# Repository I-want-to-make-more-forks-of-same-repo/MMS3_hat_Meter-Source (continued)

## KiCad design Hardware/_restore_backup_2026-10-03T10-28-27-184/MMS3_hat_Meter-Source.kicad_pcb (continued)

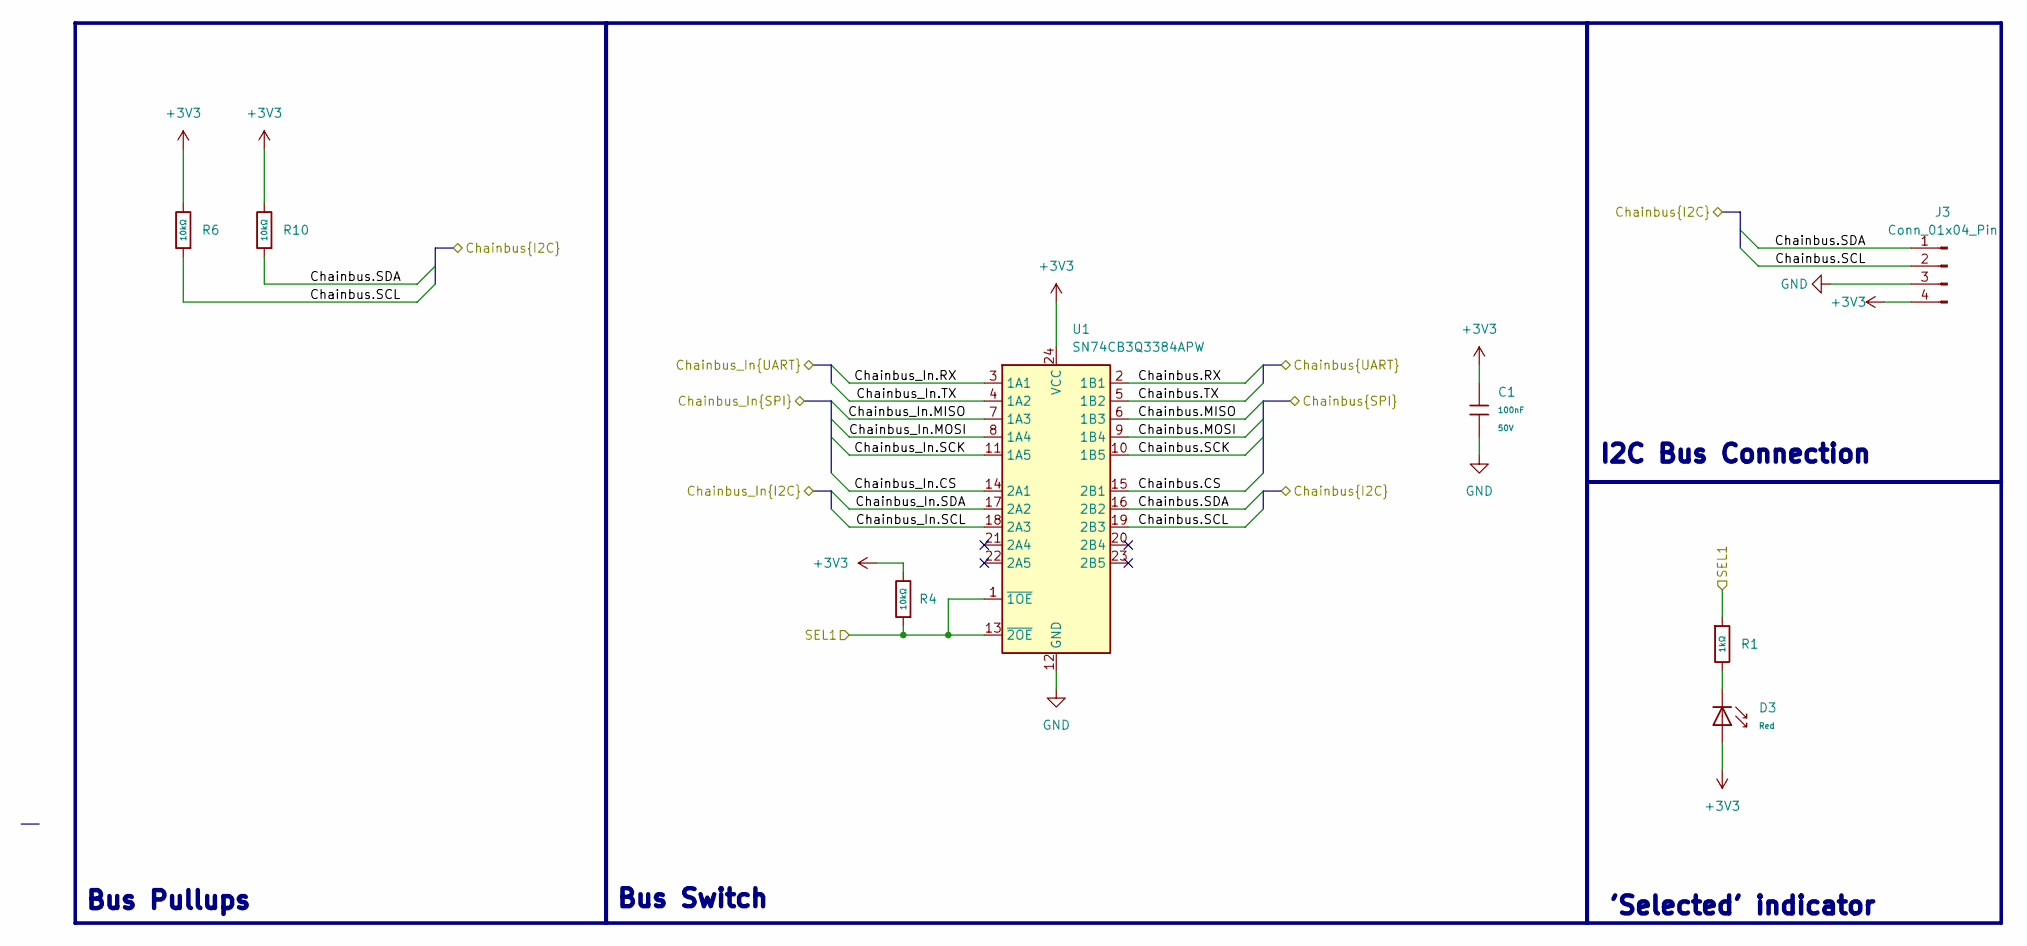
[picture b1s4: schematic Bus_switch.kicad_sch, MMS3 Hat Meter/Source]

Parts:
C1: 100nF; C_0603; Voltage Rated 50V; Tolerance ±10%; Part CC0603KRX7R9BB104; LCSC C14663
D3: Red; D_0603; Part KT-0603R; LCSC C2286
J3: Conn_01x04_Pin; PinHeader_1x04_P2.54mm_Vertical
R1: 1kΩ; R_0603; Overload Voltage (Max) 75V; Tolerance ±1%; Part 0603WAF1001T5E; LCSC C21190
R4, R6, R10: 10kΩ; R_0603; Overload Voltage (Max) 75V; Tolerance ±1%; Part 0603WAF1002T5E; LCSC C25804
U1: SN74CB3Q3384APW; TSSOP-24_4.4x7.8mm_P0.65mm; LCSC C469874

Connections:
+3V3: C1.1, D3.2, J3.4, R4.2, R6.2, R10.2, U1.24 (VCC); also elsewhere on the board
/Bus_switch/Chainbus.CS: U1.15 (2B1)
/Bus_switch/Chainbus.MISO: U1.6 (1B3)
/Bus_switch/Chainbus.MOSI: U1.9 (1B4)
/Bus_switch/Chainbus.RX: U1.2 (1B1)
/Bus_switch/Chainbus.SCK: U1.10 (1B5)
/Bus_switch/Chainbus.SCL: J3.2, R6.1, U1.19 (2B3); also elsewhere on the board
/Bus_switch/Chainbus.SDA: J3.1, R10.1, U1.16 (2B2); also elsewhere on the board
/Bus_switch/Chainbus.TX: U1.5 (1B2)
/Bus_switch/Chainbus_In.CS: U1.14 (2A1)
/Bus_switch/Chainbus_In.MISO: U1.7 (1A3)
/Bus_switch/Chainbus_In.MOSI: U1.8 (1A4)
/Bus_switch/Chainbus_In.RX: U1.3 (1A1)
/Bus_switch/Chainbus_In.SCK: U1.11 (1A5)
/Bus_switch/Chainbus_In.SCL: U1.18 (2A3); also elsewhere on the board
/Bus_switch/Chainbus_In.SDA: U1.17 (2A2); also elsewhere on the board
/Bus_switch/Chainbus_In.TX: U1.4 (1A2)
/Bus_switch/SEL1: R1.1, R4.1, U1.1 (~1OE), U1.13 (~2OE); also elsewhere on the board
GND: C1.2, J3.3, U1.12 (GND); also elsewhere on the board
unnamed: D3.1, R1.2

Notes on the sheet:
Bus Switch
'Selected' indicator
Bus Pullups
I2C Bus Connection

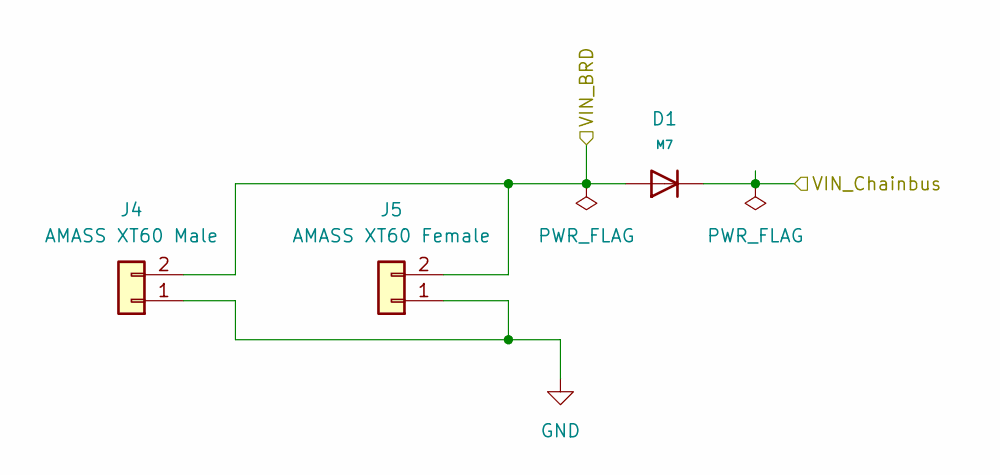
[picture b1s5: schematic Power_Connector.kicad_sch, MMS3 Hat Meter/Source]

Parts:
D1: M7; D_SMA; Forward Voltage (Vf@If) 1.1V@1A; Reverse Voltage (Vr) 1kV; Part M7; LCSC C95872
J4: AMASS XT60 Male; AMASS_XT60PW-M_1x02_P7.20mm_Horizontal; LCSC C98732
J5: AMASS XT60 Female; AMASS_XT60PW-F_1x02_P7.20mm_Horizontal; LCSC C428722

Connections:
/Power Connector/VIN_BRD: D1.2, J4.2, J5.2
GND: J4.1, J5.1; also elsewhere on the board
VIN_CHAINBUS: D1.1; also elsewhere on the board

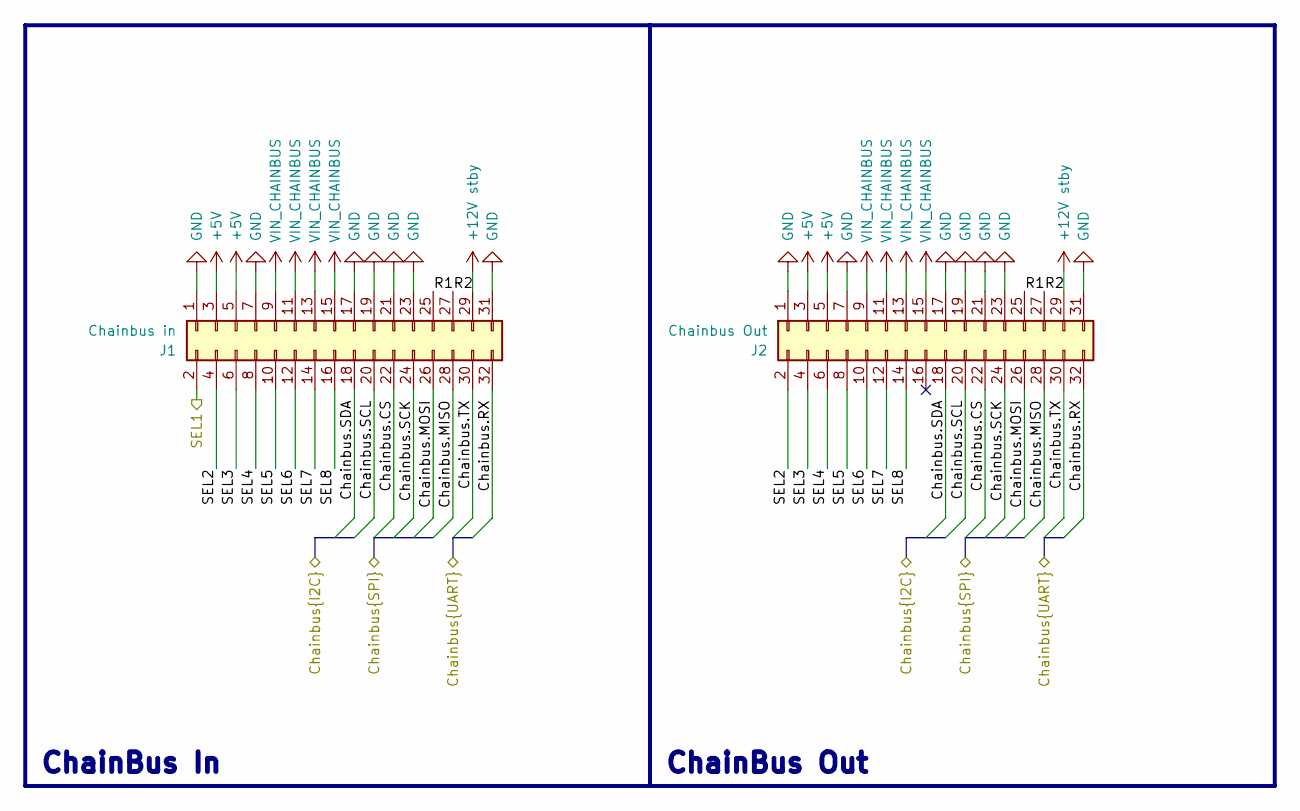
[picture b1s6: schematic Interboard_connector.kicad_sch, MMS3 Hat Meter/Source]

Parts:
J1: Chainbus in; PinHeader_2x16_P2.54mm_Vertical_SMD
J2: Chainbus Out; PinSocket_2x16_P2.54mm_Vertical_SMD

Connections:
+5V: J1.3, J1.5, J2.3, J2.5; also elsewhere on the board
+12V stby: J1.29, J2.29
/Bus_switch/Chainbus_In.SCL: J1.20, J2.20; also elsewhere on the board
/Bus_switch/Chainbus_In.SDA: J1.18, J2.18; also elsewhere on the board
/Bus_switch/SEL1: J1.2; also elsewhere on the board
/Interboard_connector/Chainbus.CS: J1.22, J2.22
/Interboard_connector/Chainbus.MISO: J1.28, J2.28
/Interboard_connector/Chainbus.MOSI: J1.26, J2.26
/Interboard_connector/Chainbus.RX: J1.32, J2.32
/Interboard_connector/Chainbus.SCK: J1.24, J2.24
/Interboard_connector/Chainbus.TX: J1.30, J2.30
/Interboard_connector/R1: J1.25, J2.25
/Interboard_connector/R2: J1.27, J2.27
/Interboard_connector/SEL2: J1.4, J2.2
/Interboard_connector/SEL3: J1.6, J2.4
/Interboard_connector/SEL4: J1.8, J2.6
/Interboard_connector/SEL5: J1.10, J2.8
/Interboard_connector/SEL6: J1.12, J2.10
/Interboard_connector/SEL7: J1.14, J2.12
/Interboard_connector/SEL8: J1.16, J2.14
GND: J1.1, J1.7, J1.17, J1.19, J1.21, J1.23, J1.31, J2.1, J2.7, J2.17, J2.19, J2.21, J2.23, J2.31; also elsewhere on the board
VIN_CHAINBUS: J1.9, J1.11, J1.13, J1.15, J2.9, J2.11, J2.13, J2.15; also elsewhere on the board

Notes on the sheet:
ChainBus In
ChainBus Out

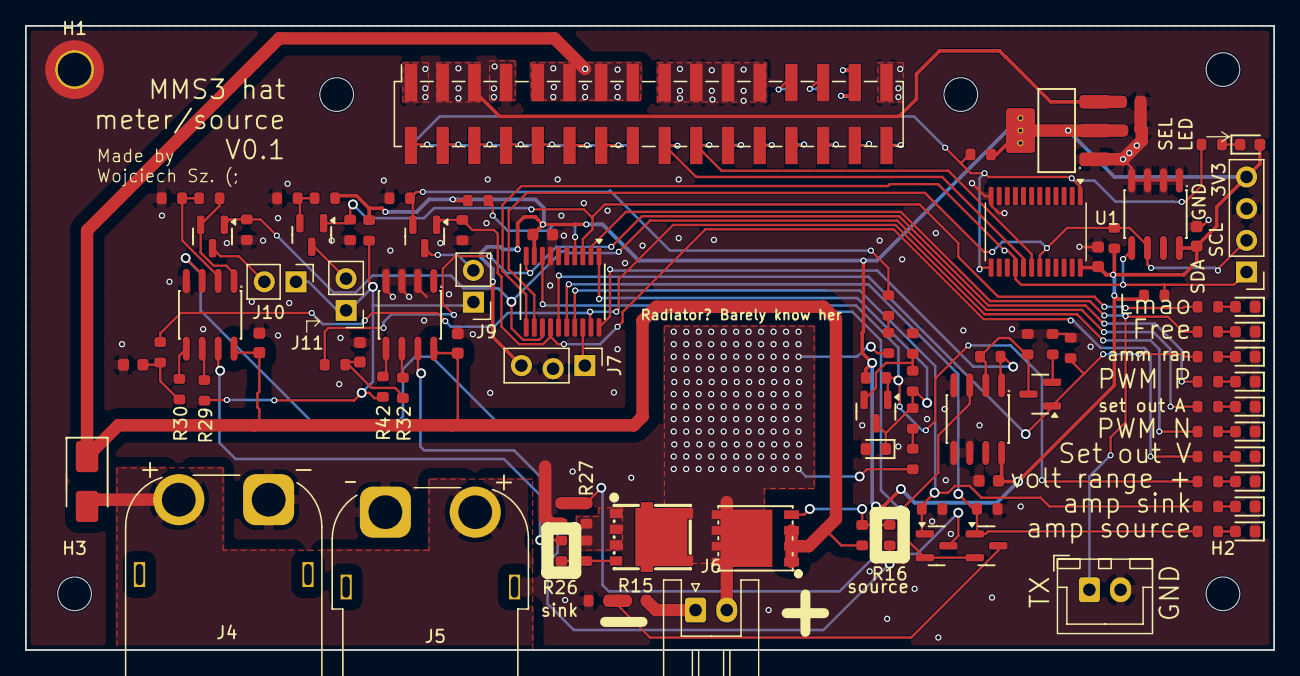
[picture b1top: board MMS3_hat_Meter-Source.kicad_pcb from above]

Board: 2 copper layers, 100.0 x 50.0 mm, 107 parts (1 on the bottom side), 80 nets.

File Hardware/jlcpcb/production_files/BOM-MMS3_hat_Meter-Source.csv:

Comment,Designator,Footprint,LCSC,Quantity
0Ω,"R15,R16,R26,R27,R29,R30,R32,R42",R_0603,C21189,8
100kΩ,"R31,R33,R58,R59",R_0603,C25803,4
100nF,"C1,C2,C6,C7,C8,C9",C_0603,C14663,6
10kΩ,"R10,R12,R19,R21,R34,R35,R36,R37,R38,R4,R41,R53,R56,R57,R6,R62",R_0603,C25804,16
10uF,"C16,C18",C_0603,C19702,2
150kΩ,"R20,R22",R_0603,C22807,2
1kΩ,"R1,R14,R17,R24,R43,R44,R45,R46,R47,R48,R49,R50,R51",R_0603,C21190,13
1uF,"C11,C12",C_0603,C15849,2
2N7002,"Q12,Q13,Q14,Q15,Q18,Q19,Q20",Q_SOT-23,C8545,7
300kΩ,"R39,R40,R60,R61,R63,R64",R_0603,C23024,6
AGM40P25A,Q4,PDFN-8_L5.8-W5.0-P1.27-LS6.1-BL,C22386140,1
AMS1117,U4,SOT-223-3_L6.5-W3.4-P2.30-LS7.0-BR,C6186,1
LM358DR2G,"U3,U6,U7",SOIC-8_L5.0-W4.0-P1.27-LS6.0-BL,C7950,3
M24C64,U2,SOIC-8_L5.0-W4.0-P1.27-LS6.0-BL,C79988,1
M7,D1,D_SMA,C95872,1
Red,"D10,D11,D12,D13,D14,D3,D4,D6,D7,D8,D9",D_0603,C2286,11
S60N04F,Q3,DFN-5_L4.9-W5.9-P1.27-LS6.2-BL,C7543820,1
SN74CB3Q3384APW,U1,TSSOP-24_4.4x7.8mm_P0.65mm,C469874,1
Conn_01x02,J6,JST_XH_S2B-XH-A_1x02_P2.50mm_Horizontal,,1
Conn_01x02,J10,PinHeader_1x02_P2.54mm_Vertical,,1
Chainbus Out,J2,PinSocket_2x16_P2.54mm_Vertical_SMD,,1
Conn_01x04_Pin,J3,PinHeader_1x04_P2.54mm_Vertical,,1
20mΩ,R18,R_0603,,1
D_Zener,D2,D_0603,,1
20mΩ,R23,R_0603,,1
Conn_01x02,J11,PinHeader_1x02_P2.54mm_Vertical,,1
Conn_01x02,J8,JST_XH_B2B-XH-A_1x02_P2.50mm_Vertical,,1
Conn_01x02,J9,PinHeader_1x02_P2.54mm_Vertical,,1
Program,J7,PinHeader_1x03_P2.54mm_Vertical,,1
CH32V003FxPx,U5,TSSOP-20_4.4x6.5mm_P0.65mm,,1
Chainbus in,J1,PinHeader_2x16_P2.54mm_Vertical_SMD,,1

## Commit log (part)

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2026-06-24 idea schematic
